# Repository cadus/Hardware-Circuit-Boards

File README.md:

# Vitalparametermodule
coming soon...

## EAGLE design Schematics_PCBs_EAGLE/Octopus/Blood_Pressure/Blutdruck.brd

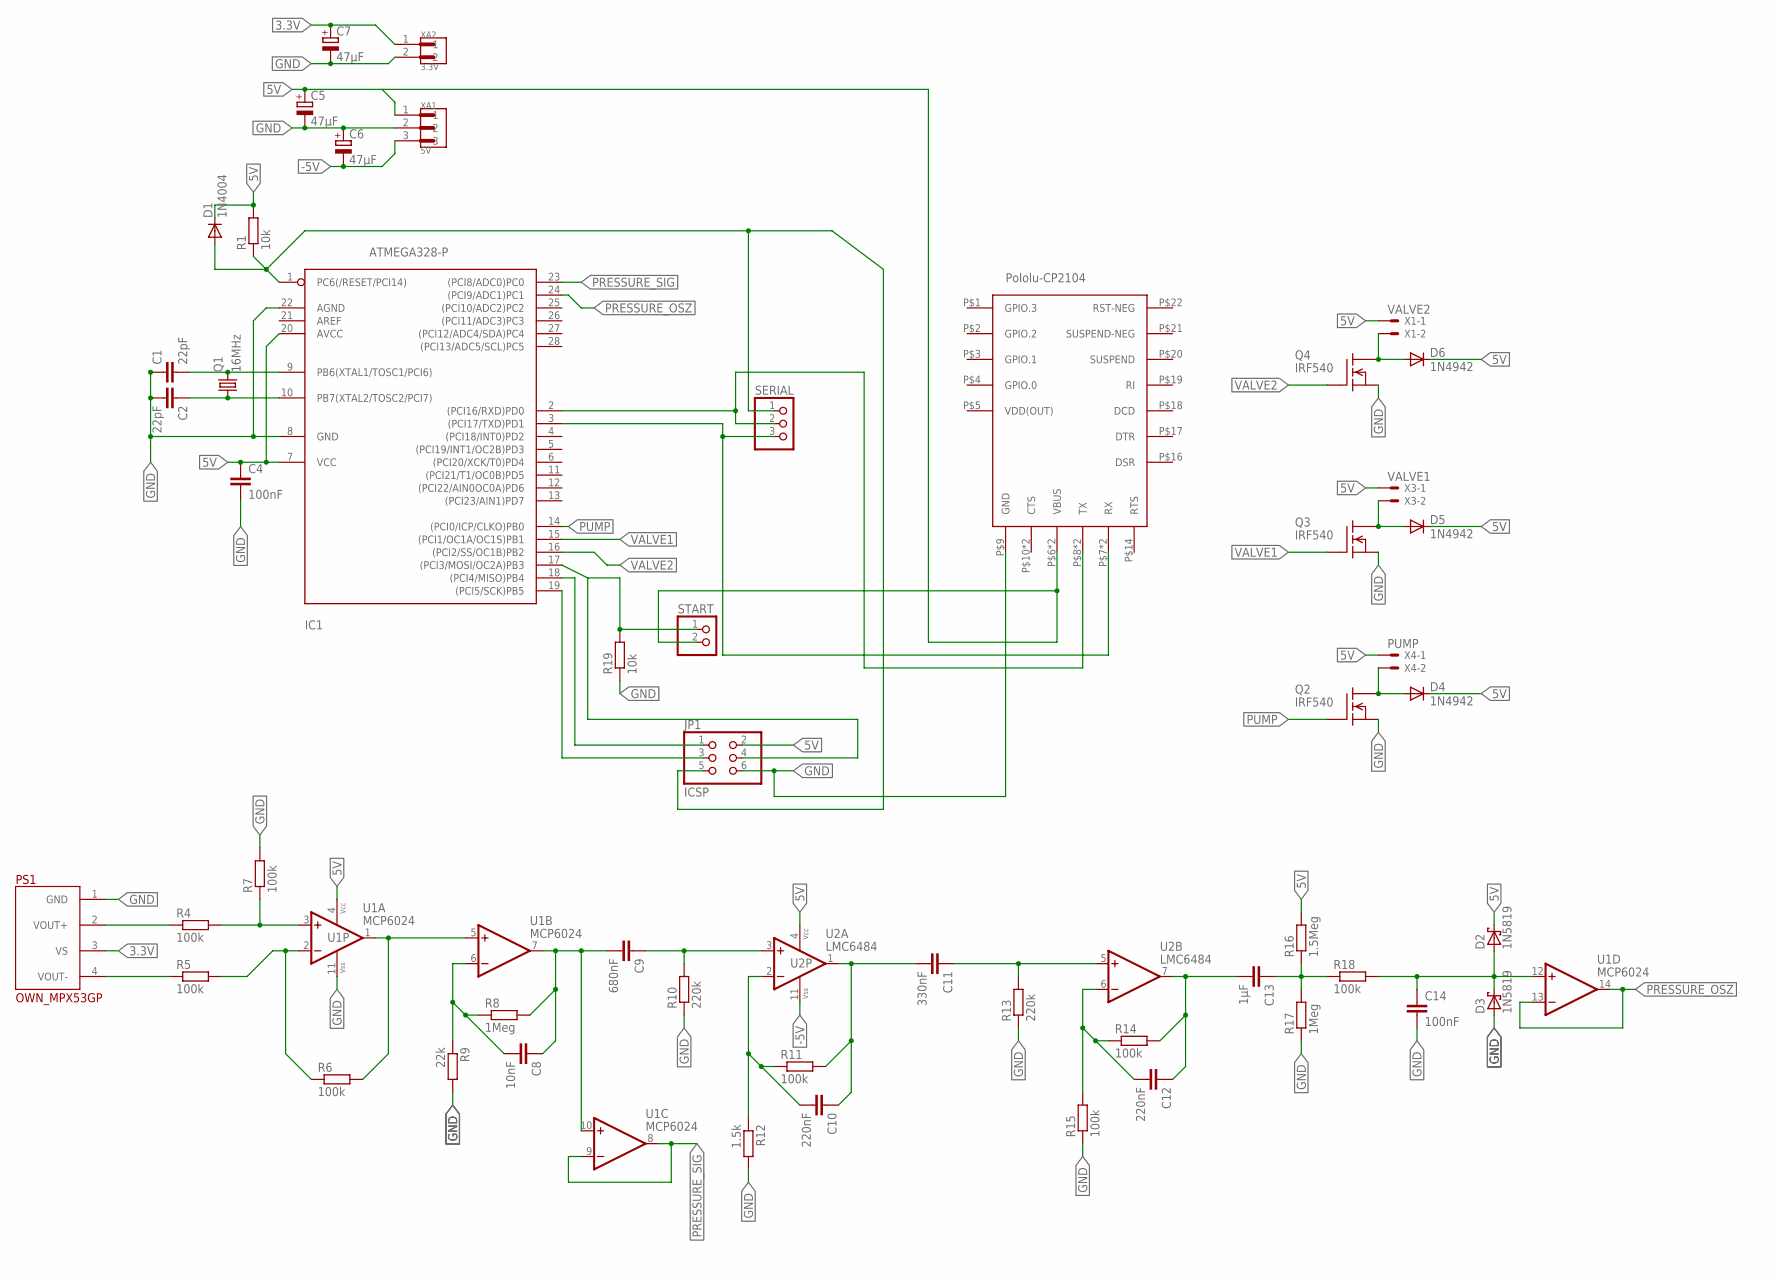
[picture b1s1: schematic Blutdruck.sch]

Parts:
C1, C2: 22pF; C025-024X044
C4, C14: 100nF; C025-024X044
C5, C6, C7: 47µF; E2,5-6E
C8: 10nF; C025-024X044
C9: 680nF; C150-064X183
C10, C12: 220nF; C025-024X044
C11: 330nF; C050-030X075
C13: 1µF; C150-072X183
D1: 1N4004; DO41-10
D2, D3: 1N5819; F126Z12
D4, D5, D6: 1N4942; DO41-10
IC1: ATMEGA328-P; DIL28-3
JP1: ICSP; 2X03
PS1: OWN_MPX53GP; MPX53
Q1: 16MHz; HC49U70
Q2, Q3, Q4: IRF540; TO220
R1, R19: 10k; 0204/7
R4, R5, R6, R7, R11, R14, R15, R18: 100k; 0204/7
R8, R17: 1Meg; 0204/7
R9: 22k; 0204/7
R10, R13: 220k; 0204/7
R12: 1.5k; 0204/7
R16: 1.5Meg; 0204/7
SERIAL: PINHD-1X3; 1X03
START: PINHD-1X2; 1X02
U1: MCP6024; DIL14
U2: LMC6484; DIL14
U$1: POLOLU_CP2104; POLOLUCP2104
X1: VALVE2; JST-XH-02-PACKAGE-LONG-PAD
X3: VALVE1; JST-XH-02-PACKAGE-LONG-PAD
X4: PUMP; JST-XH-02-PACKAGE-LONG-PAD
XA1: 5V; JST_B3P-VH(LF)(SN)
XA2: 3.3V; JST_B2P-VH(LF)(SN)

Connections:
3.3V: C7.+, PS1.3 (VS), XA2.1
5V: C4.1, C5.+, D1.C, D2.C, D4.C, D5.C, D6.C, IC1.7 (VCC), IC1.20 (AVCC), JP1.2, R1.2, R16.2, START.2, U1.4 (VCC+), U2.4 (VCC+), U$1.P$6 (VBUS), U$1.P$11 (VBUS), X1.1, X3.1, X4.1, XA1.1
-5V: C6.-, U2.11 (VCC-), XA1.3
GND: C1.1, C2.2, C4.2, C5.-, C6.+, C7.-, C14.2, D3.A, IC1.8 (GND), IC1.22 (AGND), JP1.6, PS1.1 (GND), Q2.3 (S), Q3.3 (S), Q4.3 (S), R7.2, R9.2, R10.1, R12.2, R13.1, R15.1, R17.1, R19.1, U1.11 (VCC-), U$1.P$9 (GND), XA1.2, XA2.2
unnamed: PS1.2 (VOUT+), R4.1
unnamed: R4.2, R7.1, U1.3 (+IN)
unnamed: PS1.4 (VOUT-), R5.1
unnamed: R5.2, R6.1, U1.2 (-IN)
unnamed: R6.2, U1.1 (OUT), U1.5 (+IN)
unnamed: C8.2, R8.1, R9.1, U1.6 (-IN)
unnamed: C8.1, C9.2, R8.2, U1.7 (OUT), U1.10 (+IN)
unnamed: C9.1, R10.2, U2.3 (+IN)
unnamed: C10.2, R11.1, R12.1, U2.2 (-IN)
unnamed: C10.1, C11.2, R11.2, U2.1 (OUT)
unnamed: C11.1, R13.2, U2.5 (+IN)
unnamed: C12.2, R14.1, R15.2, U2.6 (-IN)
unnamed: C12.1, C13.2, R14.2, U2.7 (OUT)
unnamed: C13.1, R16.1, R17.2, R18.1
unnamed: C14.1, D2.A, D3.C, R18.2, U1.12 (+IN)
unnamed: D4.A, Q2.2 (D), X4.2
unnamed: D5.A, Q3.2 (D), X3.2
unnamed: D6.A, Q4.2 (D), X1.2
unnamed: IC1.17 ((PCI3/MOSI/OC2A)PB3), JP1.4, R19.2, START.1
unnamed: IC1.2 ((PCI16/RXD)PD0), SERIAL.2, U$1.P$8 (TX), U$1.P$12 (TX)
unnamed: IC1.3 ((PCI17/TXD)PD1), SERIAL.3, U$1.P$7 (RX), U$1.P$13 (RX)
unnamed: C1.2, IC1.9 (PB6(XTAL1/TOSC1/PCI6)), Q1.2
unnamed: C2.1, IC1.10 (PB7(XTAL2/TOSC2/PCI7)), Q1.1
unnamed: IC1.18 ((PCI4/MISO)PB4), JP1.1
unnamed: IC1.19 ((PCI5/SCK)PB5), JP1.3
PRESSURE_OSZ: IC1.24 ((PCI9/ADC1)PC1), U1.13 (-IN), U1.14 (OUT)
PRESSURE_SIG: IC1.23 ((PCI8/ADC0)PC0), U1.8 (OUT), U1.9 (-IN)
PUMP: IC1.14 ((PCI0/ICP/CLKO)PB0), Q2.1 (G)
RESET: D1.A, IC1.1 (PC6(/RESET/PCI14)), JP1.5, R1.1, SERIAL.1
VALVE1: IC1.15 ((PCI1/OC1A/OC1S)PB1), Q3.1 (G)
VALVE2: IC1.16 ((PCI2/SS/OC1B)PB2), Q4.1 (G)
VDD(OUT): U$1.P$5 (VDD(OUT))

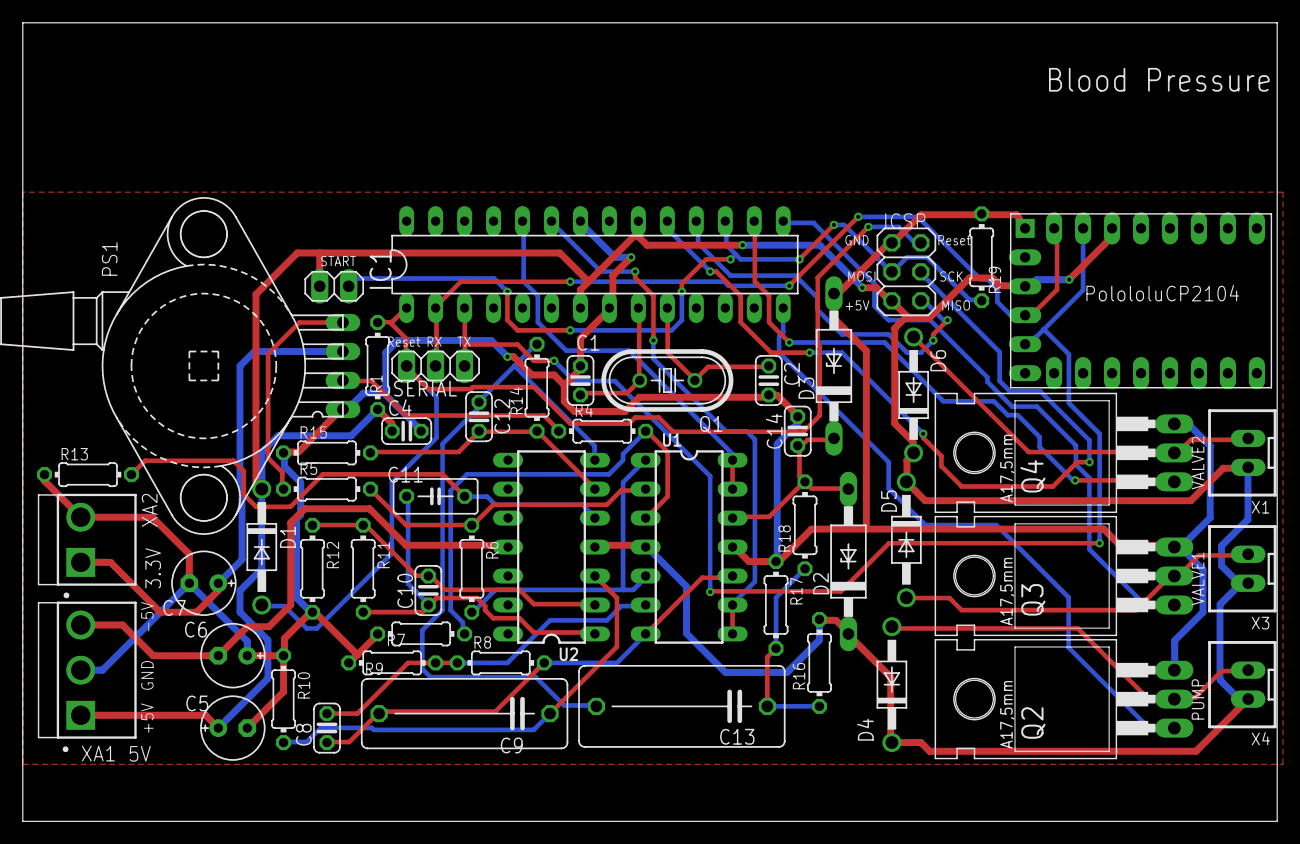
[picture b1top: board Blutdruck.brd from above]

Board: 2 copper layers, 110.0 x 70.0 mm, 53 parts (0 on the bottom side), 35 nets.

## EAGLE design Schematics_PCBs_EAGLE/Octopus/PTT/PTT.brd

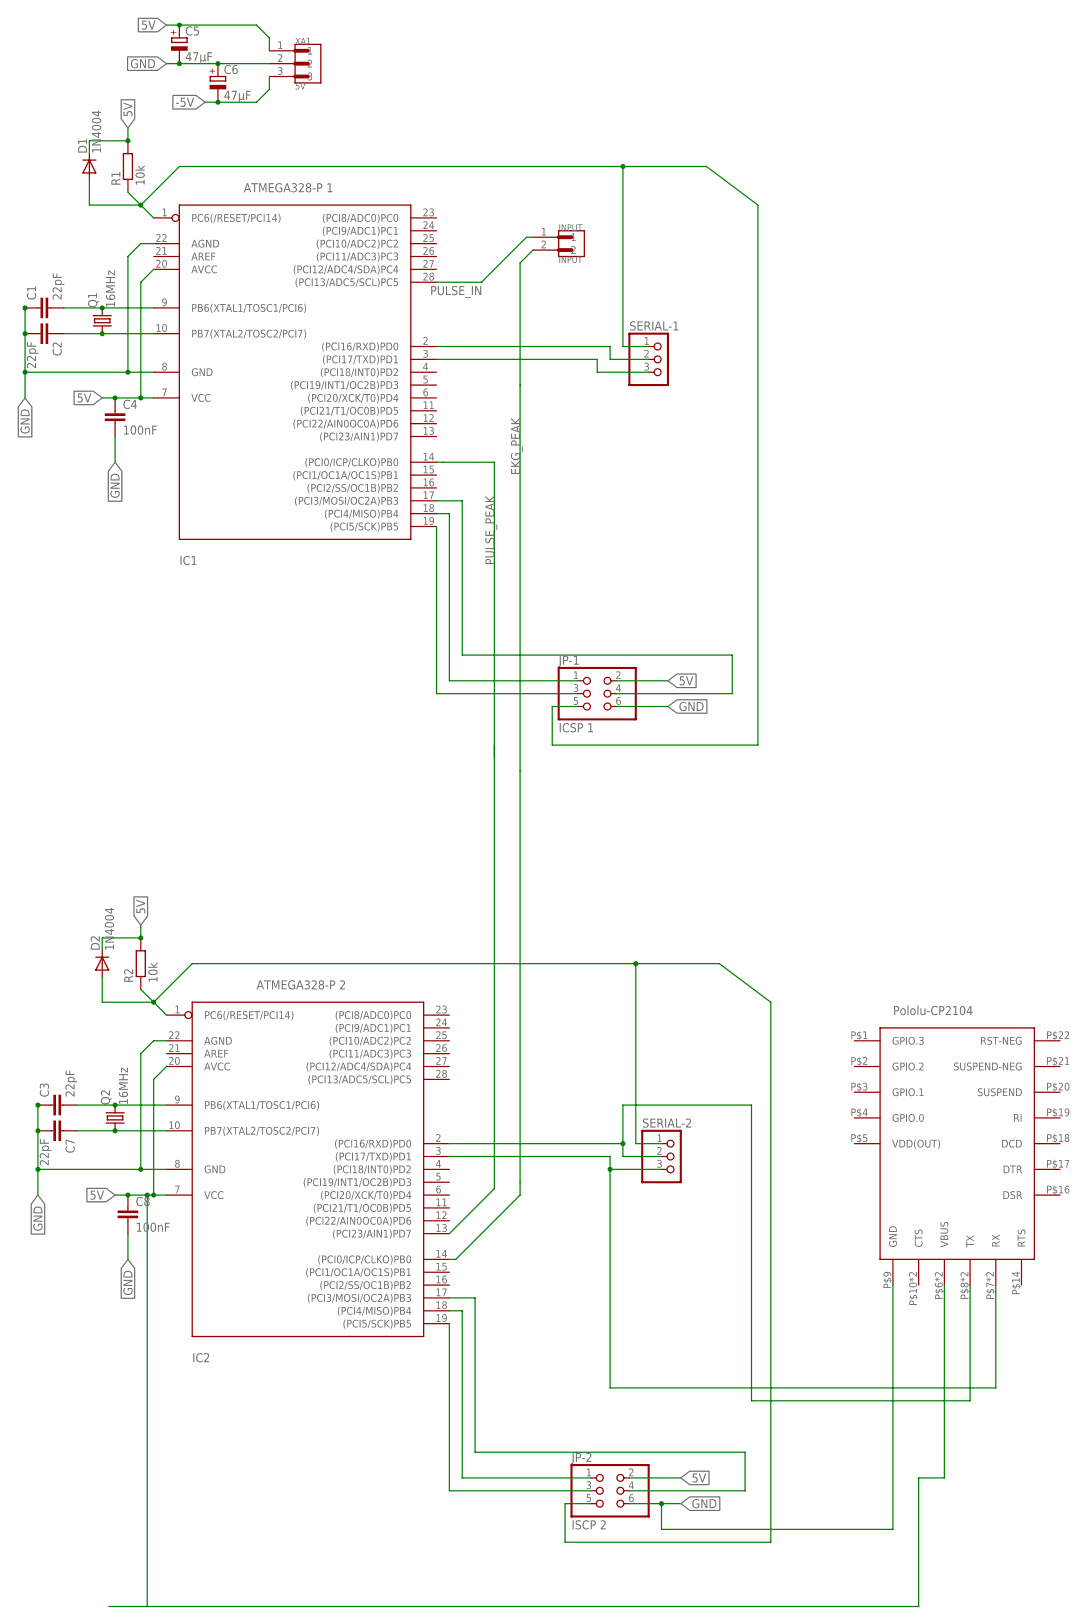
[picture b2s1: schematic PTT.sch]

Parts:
C1, C2, C3, C7: 22pF; C025-024X044
C4, C8: 100nF; C025-024X044
C5, C6: 47µF; E2,5-6E
D1, D2: 1N4004; DO41-10
IC1: ATMEGA328-P 1; DIL28-3
IC2: ATMEGA328-P 2; DIL28-3
INPUT: INPUT; JST_B2P-VH(LF)(SN)
JP-1: ICSP 1; 2X03
JP-2: ISCP 2; 2X03
Q1, Q2: 16MHz; HC49U70
R1, R2: 10k; 0204/7
SERIAL-1, SERIAL-2: PINHD-1X3; 1X03
U$2: POLOLU_CP2104; POLOLUCP2104
XA1: 5V; JST_B3P-VH(LF)(SN)

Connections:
5V: C4.1, C5.+, C8.1, D1.C, D2.C, IC1.7 (VCC), IC1.20 (AVCC), IC2.7 (VCC), IC2.20 (AVCC), JP-1.2, JP-2.2, R1.2, R2.2, U$2.P$6 (VBUS), U$2.P$11 (VBUS), XA1.1
-5V: C6.-, XA1.3
EKG_PEAK: IC2.14 ((PCI0/ICP/CLKO)PB0), INPUT.2
GND: C1.1, C2.2, C3.1, C4.2, C5.-, C6.+, C7.2, C8.2, IC1.8 (GND), IC1.22 (AGND), IC2.8 (GND), IC2.22 (AGND), JP-1.6, JP-2.6, U$2.P$9 (GND), XA1.2
unnamed: C3.2, IC2.9 (PB6(XTAL1/TOSC1/PCI6)), Q2.2
unnamed: C7.1, IC2.10 (PB7(XTAL2/TOSC2/PCI7)), Q2.1
unnamed: IC2.18 ((PCI4/MISO)PB4), JP-2.1
unnamed: IC2.19 ((PCI5/SCK)PB5), JP-2.3
unnamed: IC2.17 ((PCI3/MOSI/OC2A)PB3), JP-2.4
unnamed: IC2.2 ((PCI16/RXD)PD0), SERIAL-2.2, U$2.P$8 (TX), U$2.P$12 (TX)
unnamed: IC2.3 ((PCI17/TXD)PD1), SERIAL-2.3, U$2.P$7 (RX), U$2.P$13 (RX)
unnamed: IC1.17 ((PCI3/MOSI/OC2A)PB3), JP-1.4
unnamed: IC1.2 ((PCI16/RXD)PD0), SERIAL-1.2
unnamed: IC1.3 ((PCI17/TXD)PD1), SERIAL-1.3
unnamed: C1.2, IC1.9 (PB6(XTAL1/TOSC1/PCI6)), Q1.2
unnamed: C2.1, IC1.10 (PB7(XTAL2/TOSC2/PCI7)), Q1.1
unnamed: IC1.18 ((PCI4/MISO)PB4), JP-1.1
unnamed: IC1.19 ((PCI5/SCK)PB5), JP-1.3
PULSE_IN: IC1.28 ((PCI13/ADC5/SCL)PC5), INPUT.1
PULSE_PEAK: IC1.14 ((PCI0/ICP/CLKO)PB0), IC2.13 ((PCI23/AIN1)PD7)
RESET: D1.A, IC1.1 (PC6(/RESET/PCI14)), JP-1.5, R1.1, SERIAL-1.1
RESET1: D2.A, IC2.1 (PC6(/RESET/PCI14)), JP-2.5, R2.1, SERIAL-2.1
VDD(OUT): U$2.P$5 (VDD(OUT))

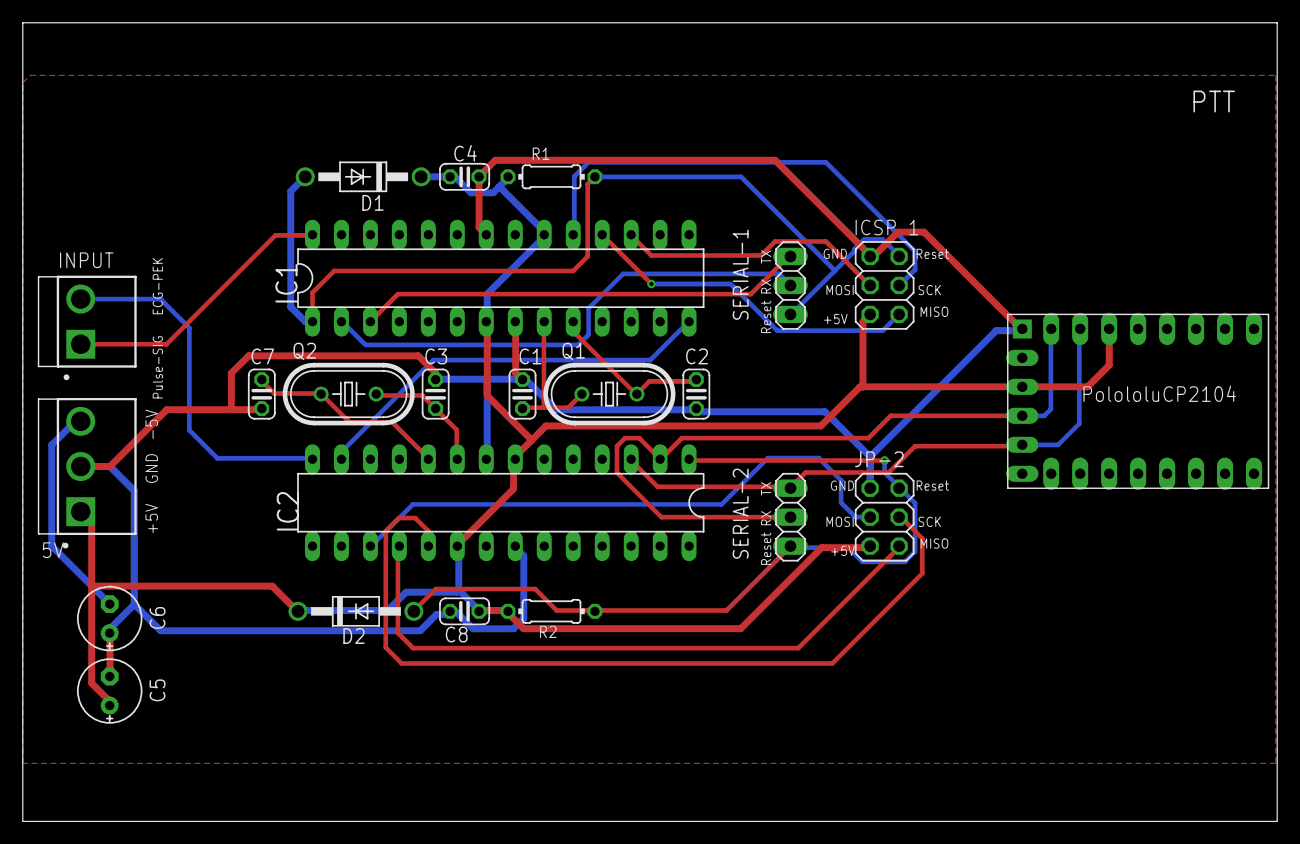
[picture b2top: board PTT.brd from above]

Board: 2 copper layers, 110.0 x 70.0 mm, 23 parts (0 on the bottom side), 22 nets.

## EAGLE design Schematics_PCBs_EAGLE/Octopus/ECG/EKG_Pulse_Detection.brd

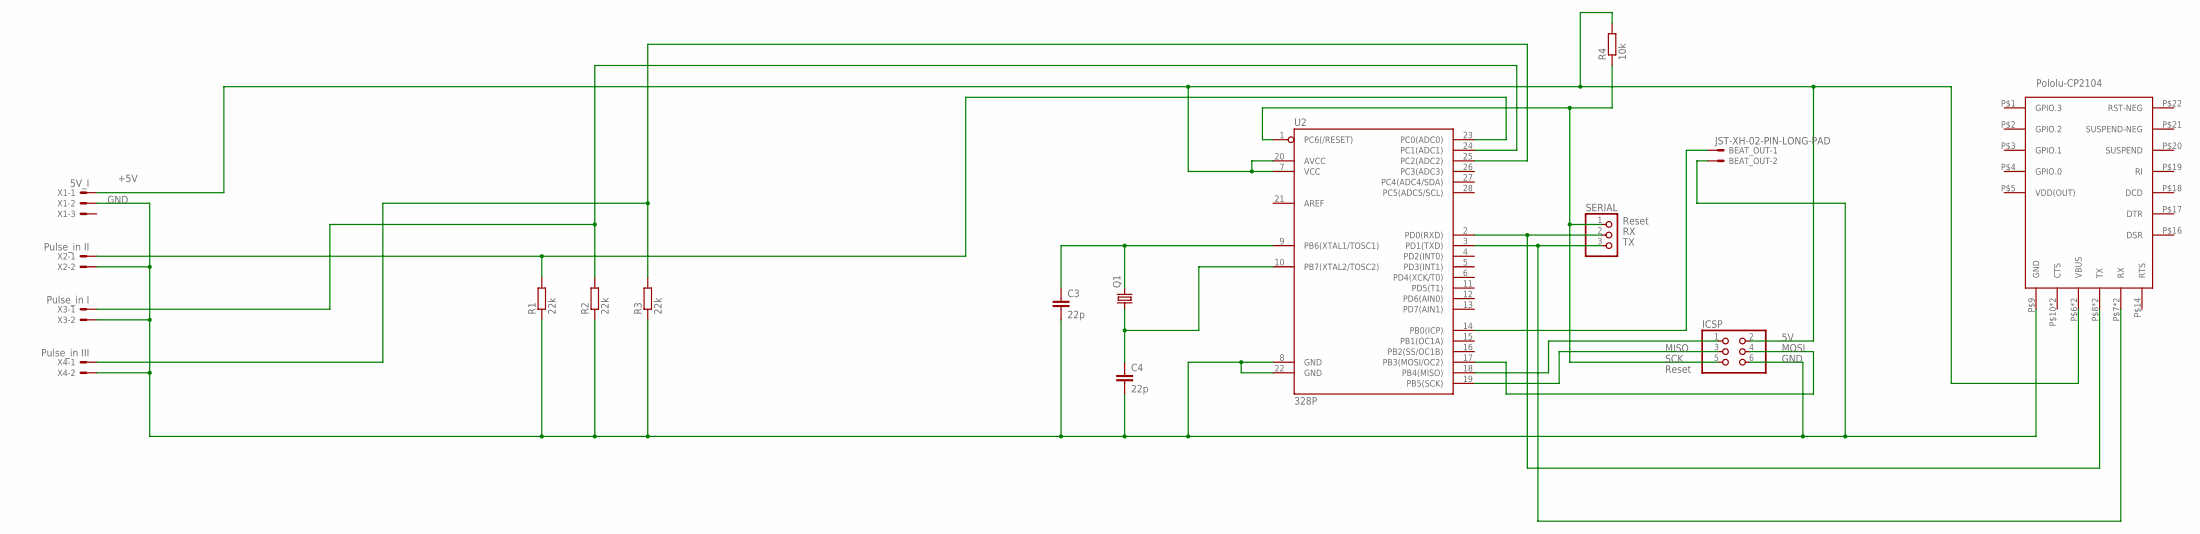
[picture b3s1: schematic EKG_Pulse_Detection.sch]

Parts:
BEAT_OUT: JST-XH-02-PIN-LONG-PAD; JST-XH-02-PACKAGE-LONG-PAD
C3, C4: 22p; C2.5-3
ICSP: PINHD-2X3; 2X03
Q1: CRYSTALHC49S; HC49/S
R1, R2, R3: 22k; 0207/7
R4: 10k; 0207/7
SERIAL: PINHD-1X3; 1X03
U2: 328P; DIP28
U$1: POLOLU_CP2104; POLOLUCP2104
X1: 5V_I; JST-XH-03-PACKAGE-LONG-PAD
X2: Pulse_in II; JST-XH-02-PACKAGE-LONG-PAD
X3: Pulse_in I; JST-XH-02-PACKAGE-LONG-PAD
X4: Pulse_in III; JST-XH-02-PACKAGE-LONG-PAD

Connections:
+5V: ICSP.2, R4.2, U2.7 (VCC), U2.20 (AVCC), U$1.P$6 (VBUS), U$1.P$11 (VBUS), X1.1
GND: BEAT_OUT.2, C3.2, C4.2, ICSP.6, R1.1, R2.1, R3.1, U2.8 (GND), U2.22 (GND), U$1.P$9 (GND), X1.2, X2.2, X3.2, X4.2
unnamed: R1.2, U2.23 (PC0(ADC0)), X2.1
unnamed: R2.2, U2.24 (PC1(ADC1)), X3.1
unnamed: R3.2, U2.25 (PC2(ADC2)), X4.1
unnamed: C3.1, Q1.2, U2.9 (PB6(XTAL1/TOSC1))
unnamed: C4.1, Q1.1, U2.10 (PB7(XTAL2/TOSC2))
unnamed: ICSP.1, U2.18 (PB4(MISO))
unnamed: ICSP.3, U2.19 (PB5(SCK))
unnamed: ICSP.4, U2.17 (PB3(MOSI/OC2))
unnamed: BEAT_OUT.1, U2.14 (PB0(ICP))
RESET: ICSP.5, R4.1, SERIAL.1, U2.1 (PC6(/RESET))
RX: SERIAL.2, U2.2 (PD0(RXD)), U$1.P$8 (TX), U$1.P$12 (TX)
TX: SERIAL.3, U2.3 (PD1(TXD)), U$1.P$7 (RX), U$1.P$13 (RX)
VDD(OUT): U$1.P$5 (VDD(OUT))

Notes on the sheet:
Reset
SCK
MISO
MOSI
GND

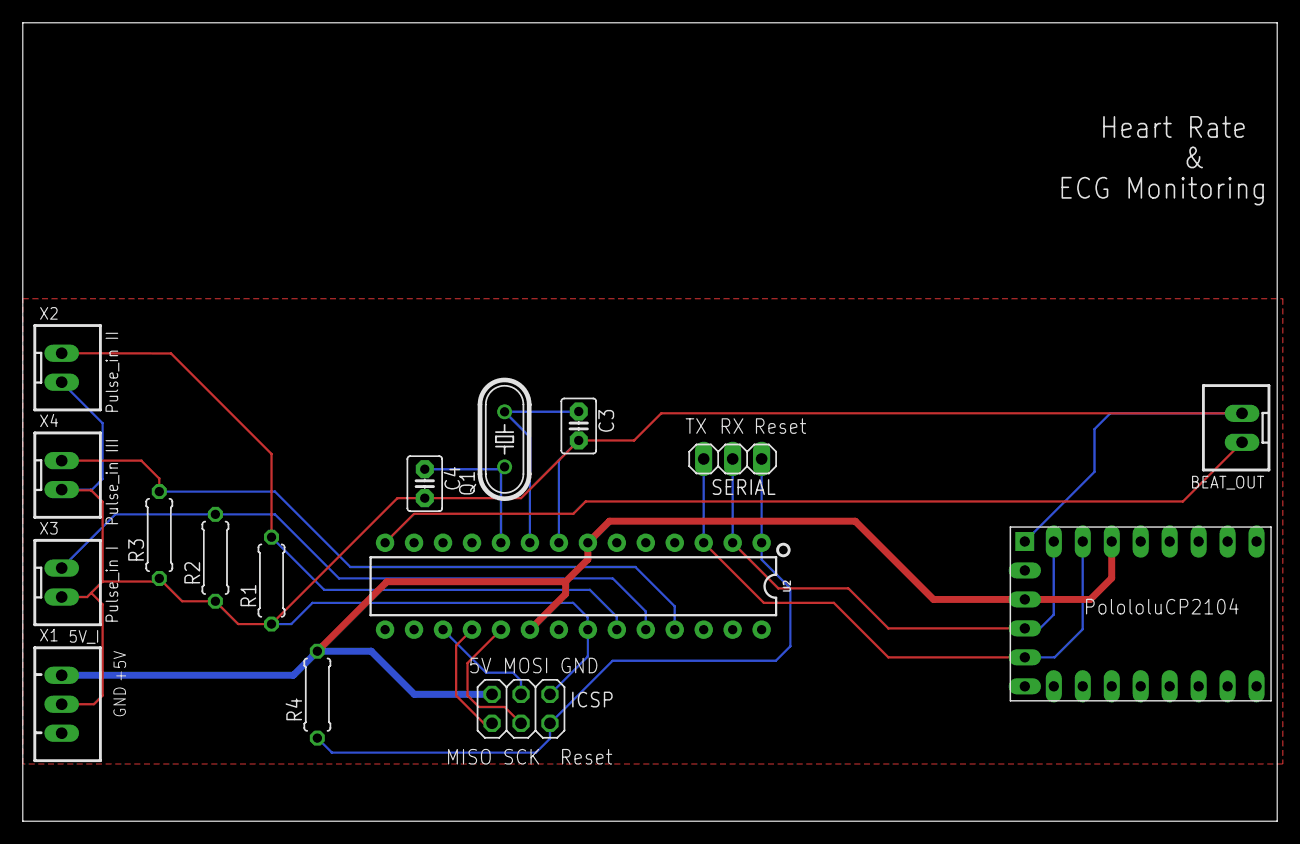
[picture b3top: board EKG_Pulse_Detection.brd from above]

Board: 2 copper layers, 110.0 x 70.0 mm, 16 parts (0 on the bottom side), 14 nets.

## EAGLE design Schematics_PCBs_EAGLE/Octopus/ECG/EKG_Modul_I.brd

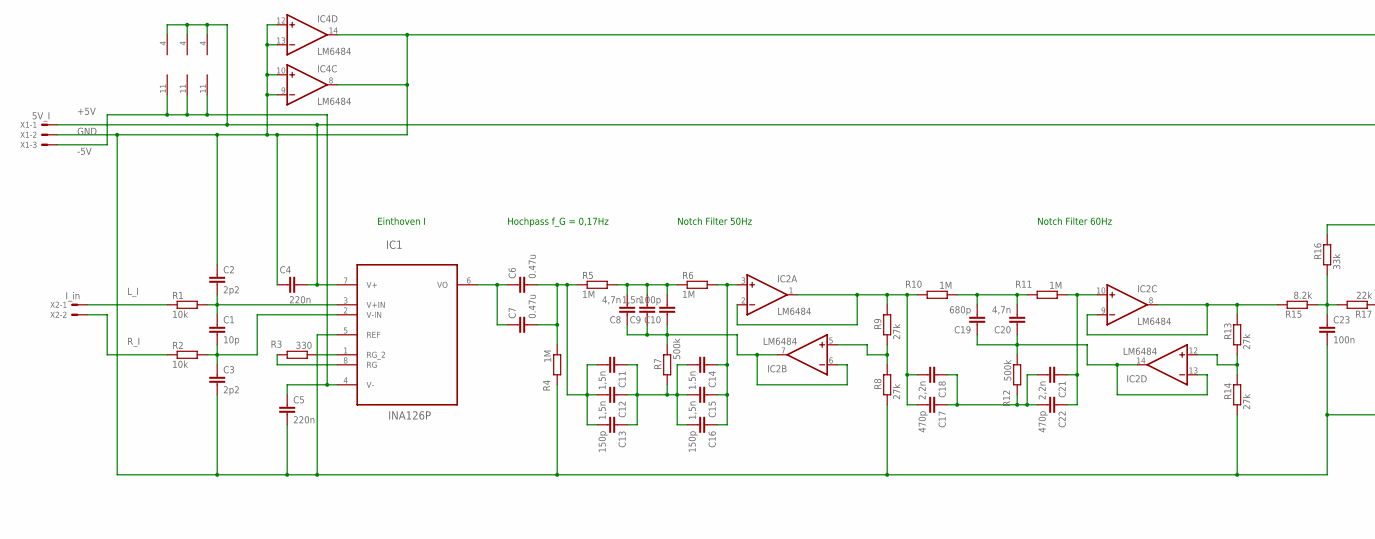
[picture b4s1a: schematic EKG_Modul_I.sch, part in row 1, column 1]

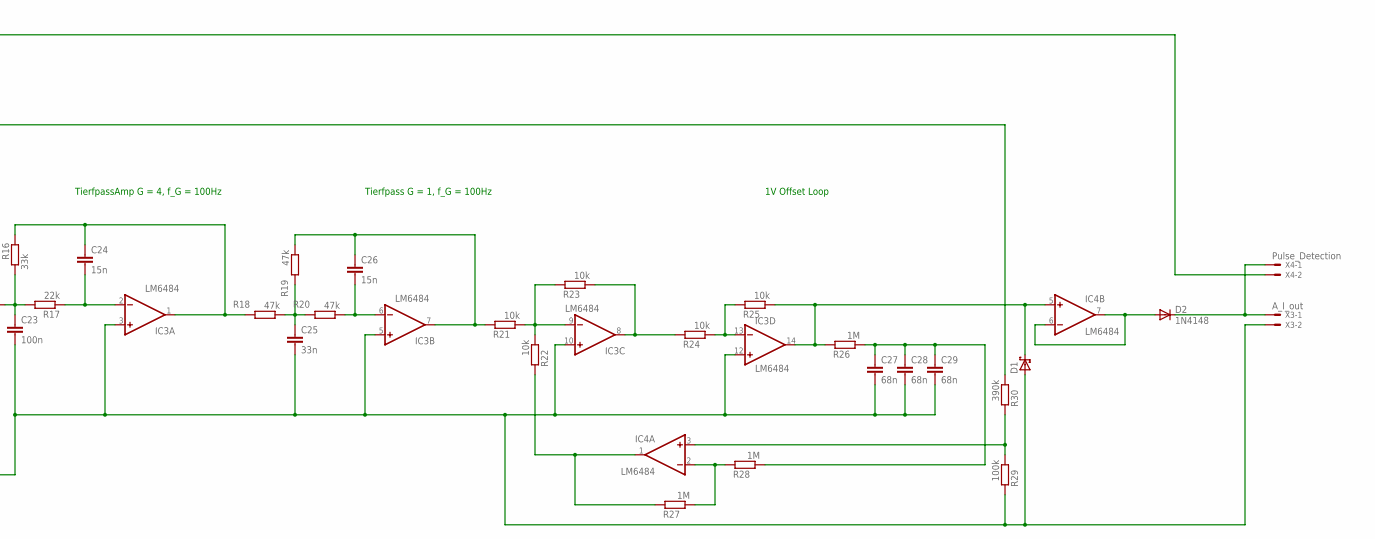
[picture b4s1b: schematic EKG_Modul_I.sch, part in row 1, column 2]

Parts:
C1: 10p; C2.5-2
C2, C3: 2p2; C2.5-2
C4, C5: 220n; C2.5-2
C6, C7: 0.47u; C15B5
C8, C20: 4,7n; C2.5-2
C9, C11, C12, C15: 1,5n; C2.5-2
C10: 100p; C2.5-2
C13, C16: 150p; C2.5-2
C14: 1.5n; C2.5-2
C17, C22: 470p; C2.5-2
C18, C21: 2,2n; C2.5-2
C19: 680p; C2.5-2
C23: 100n; C2.5-2
C24, C26: 15n; C2.5-2
C25: 33n; C2.5-2
C27, C28, C29: 68n; C2.5-2
D1: SCHOTTKY-DIODEDO35-7; DO35-7
D2: 1N4148; DO35-7
IC1: INA126P; DIP254P762X508-8
IC2, IC3, IC4: LM6484; DIL14
R1, R2, R21, R22, R23, R24, R25: 10k; 0207/7
R3: 330; 0207/7
R4, R5, R6, R10, R11, R26, R27, R28: 1M; 0207/7
R7, R12: 500k; 0207/7
R8, R9, R13, R14: 27k; 0207/7
R15: 8.2k; 0207/7
R16: 33k; 0207/7
R17: 22k; 0207/7
R18, R19, R20: 47k; 0207/7
R29: 100k; 0207/7
R30: 390k; 0207/7
X1: 5V_I; JST-XH-03-PACKAGE-LONG-PAD
X2: I_in; JST-XH-02-PACKAGE-LONG-PAD
X3: A_I_out; JST-XH-02-PACKAGE-LONG-PAD
X4: Pulse_Detection; JST-XH-02-PACKAGE-LONG-PAD

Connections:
+5V: C4.2, IC1.7 (V+), IC2.4 (V+), IC3.4 (V+), IC4.4 (V+), R30.1, X1.1
-5V: C5.1, IC1.4 (V-), IC2.11 (V-), IC3.11 (V-), IC4.11 (V-), X1.3
GND: C2.1, C3.2, C4.1, C5.2, C23.2, C25.2, C27.2, C28.2, C29.2, D1.A, IC1.5 (REF), IC3.3 (+IN), IC3.5 (+IN), IC3.10 (+IN), IC3.12 (+IN), IC4.8 (OUT), IC4.9 (-IN), IC4.10 (+IN), IC4.12 (+IN), IC4.13 (-IN), IC4.14 (OUT), R4.2, R8.1, R14.1, R29.2, X1.2, X3.2, X4.2
L_I: R1.1, X2.1
unnamed: D2.A, IC4.6 (-IN), IC4.7 (OUT)
unnamed: D2.C, X3.1, X4.1
unnamed: C1.1, C2.2, IC1.3 (V+IN), R1.2
unnamed: C1.2, C3.1, IC1.2 (V-IN), R2.2
unnamed: IC1.1 (RG_2), R3.1
unnamed: IC1.8 (RG), R3.2
unnamed: C6.1, C7.1, IC1.6 (VO)
unnamed: C6.2, C7.2, C11.2, C12.2, C13.2, R4.1, R5.1
unnamed: C17.2, C18.2, IC2.1 (OUT), IC2.2 (-IN), R9.2, R10.2
unnamed: C8.2, C9.2, C10.2, R5.2, R6.1
unnamed: C11.1, C12.1, C13.1, C14.2, C15.2, C16.2, R7.1
unnamed: C14.1, C15.1, C16.1, IC2.3 (+IN), R6.2
unnamed: IC2.8 (OUT), IC2.9 (-IN), R13.2, R15.2
unnamed: IC2.5 (+IN), R8.2, R9.1
unnamed: C24.1, IC3.1 (OUT), R16.2, R18.2
unnamed: C19.2, C20.2, R10.1, R11.2
unnamed: C23.1, R15.1, R16.1, R17.2
unnamed: C17.1, C18.1, C21.2, C22.2, R12.2
unnamed: C21.1, C22.1, IC2.10 (+IN), R11.1
unnamed: C19.1, C20.1, IC2.13 (-IN), IC2.14 (OUT), R12.1
unnamed: C24.2, IC3.2 (-IN), R17.1
unnamed: IC2.12 (+IN), R13.1, R14.2
unnamed: IC3.13 (-IN), R24.1, R25.2
unnamed: C26.2, IC3.6 (-IN), R20.1
unnamed: C25.1, R18.1, R19.2, R20.2
unnamed: IC3.9 (-IN), R21.1, R22.1, R23.2
unnamed: C26.1, IC3.7 (OUT), R19.1, R21.2
unnamed: IC3.8 (OUT), R23.1, R24.2
unnamed: C8.1, C9.1, C10.1, IC2.6 (-IN), IC2.7 (OUT), R7.2
unnamed: D1.C, IC3.14 (OUT), IC4.5 (+IN), R25.1, R26.2
unnamed: IC4.1 (OUT), R22.2, R27.2
unnamed: IC4.2 (-IN), R27.1, R28.2
unnamed: C27.1, C28.1, C29.1, R26.1, R28.1
unnamed: IC4.3 (+IN), R29.1, R30.2
R_I: R2.1, X2.2

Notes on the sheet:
Einthoven I
Hochpass f_G = 0,17Hz
Notch Filter 50Hz
Notch Filter 60Hz
Tierfpass G = 1, f_G = 100Hz
TierfpassAmp G = 4, f_G = 100Hz
1V Offset Loop

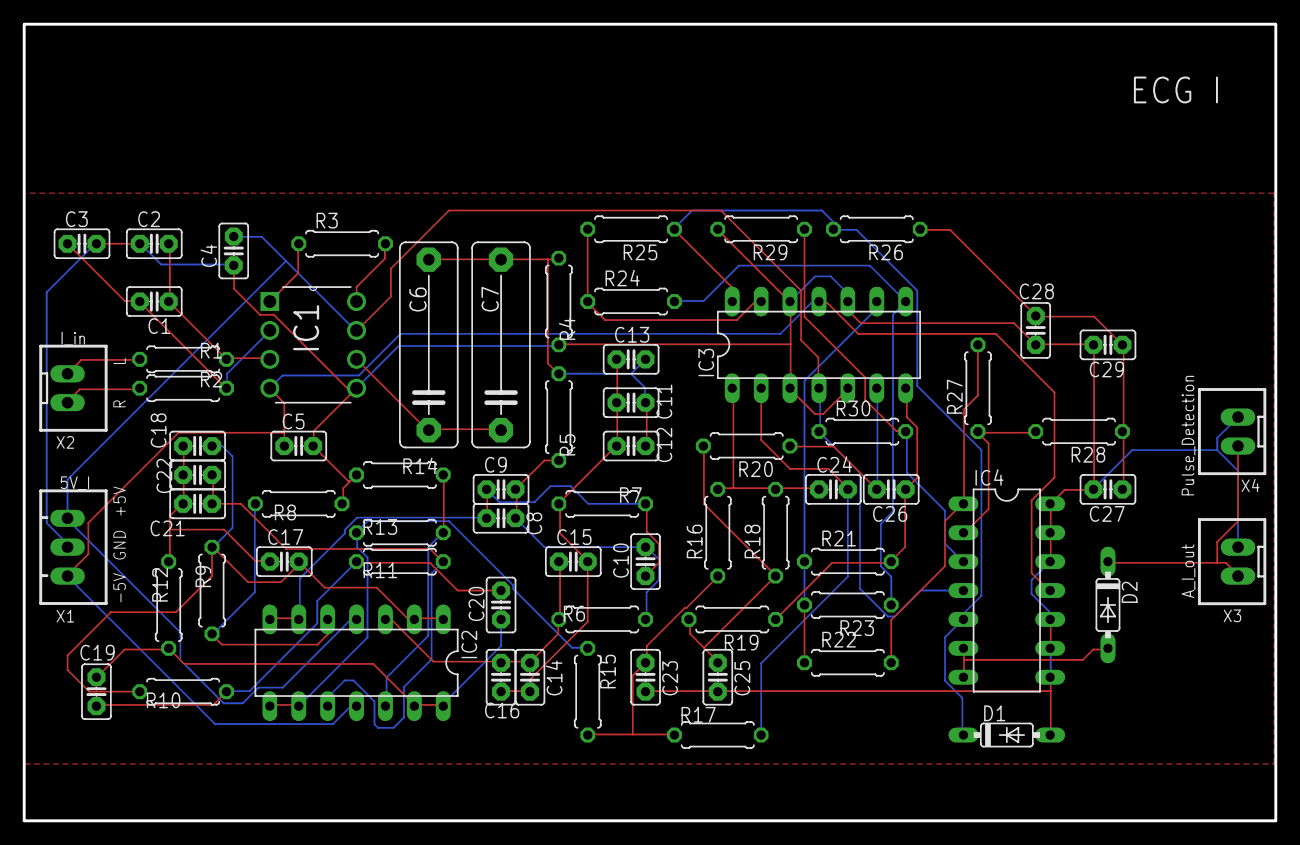
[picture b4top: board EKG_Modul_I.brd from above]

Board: 2 copper layers, 110.0 x 70.0 mm, 69 parts (0 on the bottom side), 39 nets.

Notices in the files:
parts and their libraries:
op-amp: Copyright (C) 2006 by Bob Starr
SparkFun-IC-Microcontroller: Licensing: Creative Commons ShareAlike 4.0 International - https://creativecommons.org/licenses/by-sa/4.0
